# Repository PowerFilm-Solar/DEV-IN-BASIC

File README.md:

# DEV-IN-BASIC
Hardware files for PowerFilm's implementation of the BQ25570

The Indoor Solar Development Kit (DEV-IN-BASIC) makes integrating indoor solar into electronics simple. It consists of an energy harvesting module with integrated power management designed and optimized for Indoor Light Series solar panels.

The DEV-IN-BASIC kit uses a nano-power boost charging technology to efficiently extract energy from the indoor solar, even in dimly lit environments down to 200 lux and below. The integrated power management can be configured to store the collected energy into various storage element technologies. An output power rail is used to provide power to external electronics. 
 
### Development Kit Layout

![Indoor Solar Development Kit](https://www.powerfilmsolar.com/media/cms/products_dev_kits_devinbasic_diagra_45B16E6200140.jpg "
Indoor Solar Development Kit layout")

### What can I power?

- BLE Beacons and Tags
- E-Paper Displays
- Telematics
- Smart Locks
- Thermostats
- Smart Windows and Shades
- Wireless Sensors
- Wearables
- Field and Herd Monitoring
- Other Low Power Electronics

### Features

- Nano power DC-DC boost charger, with 100mV minimum input voltage.
- Integrated power management.
- Compatible with Li-ion, LiFePo, Thin-Film, capacitor, and supercapacitor rechargeable battery technologies.
- Adjustable battery under-voltage protection and load disconnect with hysteresis. 
- Adjustable battery overvoltage protection.
- Regulated output power rail with adjustable output voltage.
- All you need is a screwdriver to jump-start your idea into reality.

### Use Cases

- Designed for artificial lighting.
- Capable of powering low power wireless RF modules and sensors.
- Well suited for applications with intermittent high current pulsing common in most wireless protocol.
 
### What’s In The Kit?
##### Board

- DEV-IN-BASIC PCBA
##### Panel

- (2) LL200-3-37 Indoor Solar Panel with Leads
##### Battery 

- Model: DTP301120
- Nominal Voltage: 3.7V
- Typical Capacity: 40 mAh
- Includes protection circuit

No international shipments for online purchases. For delivery to other locations, please order via [Digi-Key](https://www.digikey.com/product-detail/en/powerfilm-inc/DEV-IN-BASIC/1996-DEV-IN-BASIC-ND/9695308) or [Mouser](https://www.mouser.com/ProductDetail/PowerFilm/DEV-IN-BASIC?qs=BJlw7L4Cy7%2Fw4dHFXPm5kg%3D%3D).
### Additional Resources

[Indoor Solar Development Kit Spec Sheet](https://www.powerfilmsolar.com/media/cms/Indoor_Solar_Development_Kit_LLDev1_083F9A3BC60A6.pdf)

[Indoor Solar Development Kit Flyer](https://www.powerfilmsolar.com/media/cms/Indoor_Solar_Development_Kit_Flyer_09CFAFE8ABEA2.pdf)

[Indoor Solar Development Kit Customization Guide](https://www.powerfilmsolar.com/media/cms/Indoor_Solar_Development_Kit_Custom_157741447633B.pdf)

[Indoor Solar Development Kit Design Files & Resources](https://www.powerfilmsolar.com/products/development-kits/indoor-solar-development-kit)

[IC (BQ25570) Data Sheet](http://www.ti.com/lit/ds/symlink/bq25570.pdf)

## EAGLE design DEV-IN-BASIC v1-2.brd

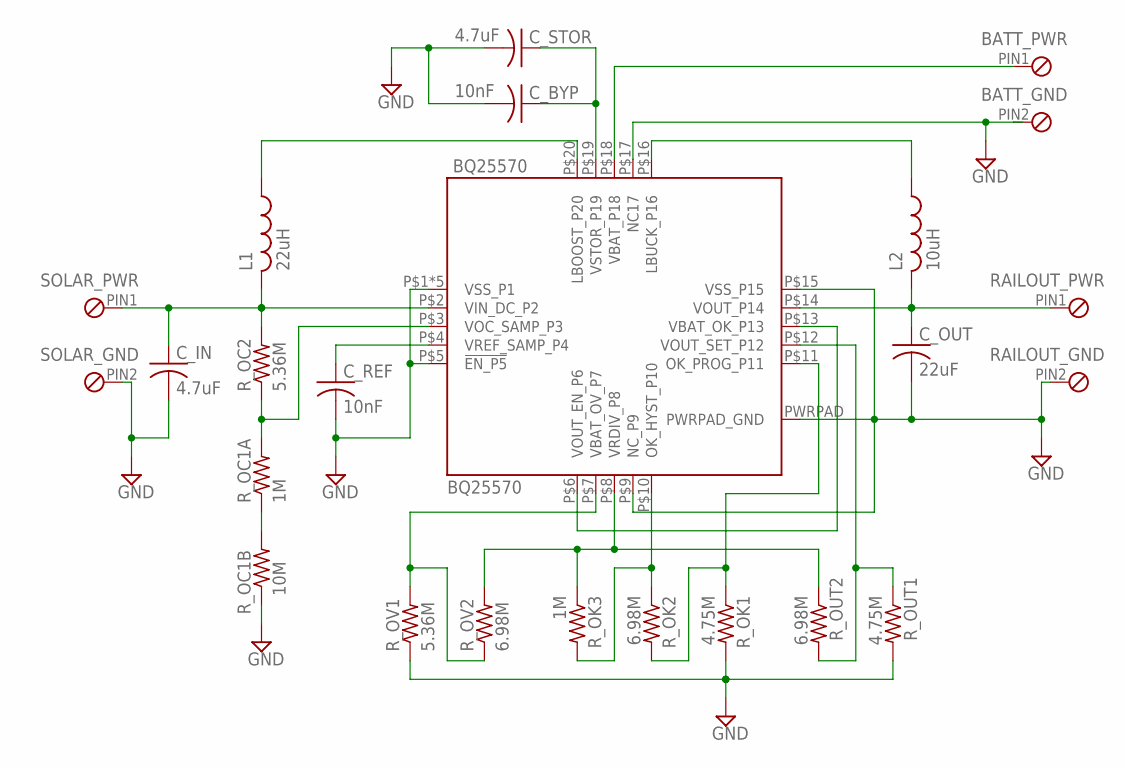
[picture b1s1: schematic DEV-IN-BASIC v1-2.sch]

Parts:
BATT_: TE_2PIN_CLARK; TE_CONN_2POS
BQ25570: BQ25570
C_BYP: 10nF; C0603; MFG_PART# CL10B103KB8SFNC
C_IN: 4.7uF; C0603; MFG_PART# CL10A475KQ8NNWC
C_OUT: 22uF; C0603; MFG_PART# GRM188R60J226MEA0D
C_REF: 10nF; C0603; MFG_PART# CL10B103KB8SFNC
C_STOR: 4.7uF; C0603; MFG_PART# CL10A475KQ8NNWC
L1: 22uH; 744031220
L2: 10uH; 744031220
RAILOUT_: TE_2PIN_CLARK; TE_CONN_2POS
R_OC1A: 1M; R0603; MFG_PART# RMCF0603FT1M00
R_OC1B: 10M; R0603; MFG_PART# RC0603FR-0710ML
R_OC2: 5.36M; R0603; MFG_PART# CRCW06035M36FKEA
R_OK1: 4.75M; R0603; MFG_PART# RC0603FR-074M75L
R_OK2: 6.98M; R0603; MFG_PART# CRCW06036M98FKEA
R_OK3: 1M; R0603; MFG_PART# RMCF0603FT1M00
R_OUT1: 4.75M; R0603; MFG_PART# RC0603FR-074M75L
R_OUT2: 6.98M; R0603; MFG_PART# CRCW06036M98FKEA
R_OV1: 5.36M; R0603; MFG_PART# CRCW06035M36FKEA
R_OV2: 6.98M; R0603; MFG_PART# CRCW06036M98FKEA
SOLAR_: TE_2PIN_CLARK; TE_CONN_2POS

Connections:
GND: BATT_.PIN2, BQ25570.P$1 (VSS_P1), BQ25570.P$5 (!EN_P5), BQ25570.P$9 (NC_P9), BQ25570.P$15 (VSS_P15), BQ25570.P$17 (NC17), BQ25570.P$21 (VSS_P1), BQ25570.P$22 (VSS_P1), BQ25570.P$23 (VSS_P1), BQ25570.P$24 (VSS_P1), BQ25570.PWRPAD (PWRPAD_GND), C_BYP.2, C_IN.2, C_OUT.2, C_REF.2, C_STOR.2, RAILOUT_.PIN2, R_OC1B.1, R_OK1.2, R_OUT1.2, R_OV1.1, SOLAR_.PIN2
LBOOST_PIN20: BQ25570.P$20 (LBOOST_P20), L1.PIN1 (1)
LBUCK_PIN16: BQ25570.P$16 (LBUCK_P16), L2.PIN1 (1)
unnamed: R_OC1A.1, R_OC1B.2
OK_HYST_PIN10: BQ25570.P$10 (OK_HYST_P10), R_OK2.1, R_OK3.2
OK_PROG_PIN11: BQ25570.P$11 (OK_PROG_P11), R_OK1.1, R_OK2.2
RAILOUT_POS: BQ25570.P$14 (VOUT_P14), C_OUT.1, L2.PIN2 (2), RAILOUT_.PIN1
SOLAR_PWR_VIN: BQ25570.P$2 (VIN_DC_P2), C_IN.1, L1.PIN2 (2), R_OC2.2, SOLAR_.PIN1
VBAT: BATT_.PIN1, BQ25570.P$18 (VBAT_P18)
VBAT_OK: BQ25570.P$6 (VOUT_EN_P6), BQ25570.P$13 (VBAT_OK_P13)
VBAT_OV_PIN7: BQ25570.P$7 (VBAT_OV_P7), R_OV1.2, R_OV2.1
VOC_SAMP_PIN3: BQ25570.P$3 (VOC_SAMP_P3), R_OC1A.2, R_OC2.1
VOUT_SET_PIN12: BQ25570.P$12 (VOUT_SET_P12), R_OUT1.1, R_OUT2.2
VRDIV_PIN8: BQ25570.P$8 (VRDIV_P8), R_OK3.1, R_OUT2.1, R_OV2.2
VREF_SAMP_PIN4: BQ25570.P$4 (VREF_SAMP_P4), C_REF.1
VSTOR: BQ25570.P$19 (VSTOR_P19), C_BYP.1, C_STOR.1

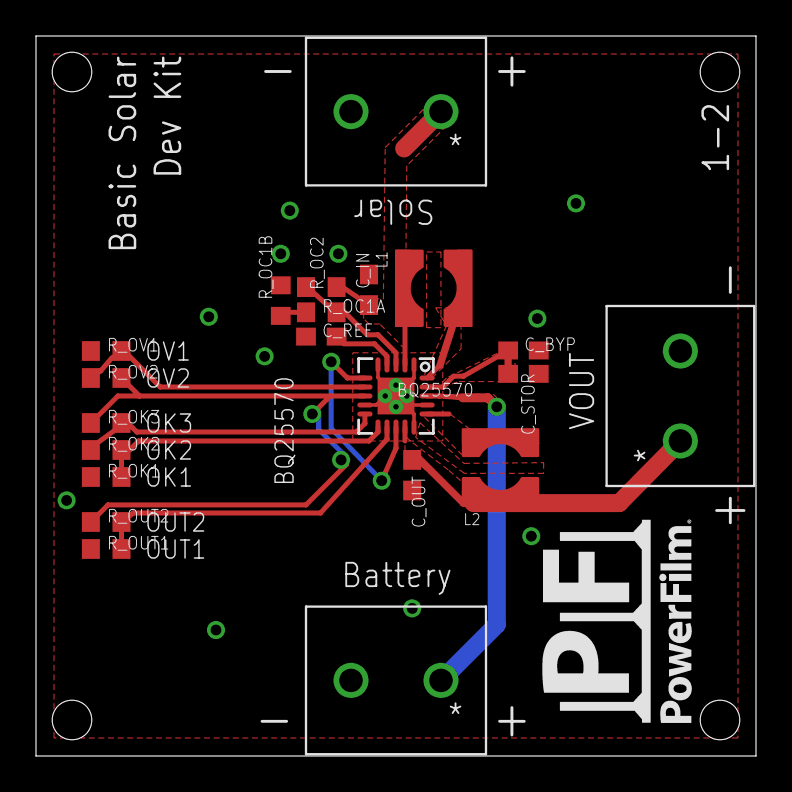
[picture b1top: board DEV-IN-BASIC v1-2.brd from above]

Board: 2 copper layers, 40.0 x 40.0 mm, 21 parts (0 on the bottom side), 16 nets.

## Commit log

2020-12-10 Added libraries
2020-12-10 Fixed unrouted trace
